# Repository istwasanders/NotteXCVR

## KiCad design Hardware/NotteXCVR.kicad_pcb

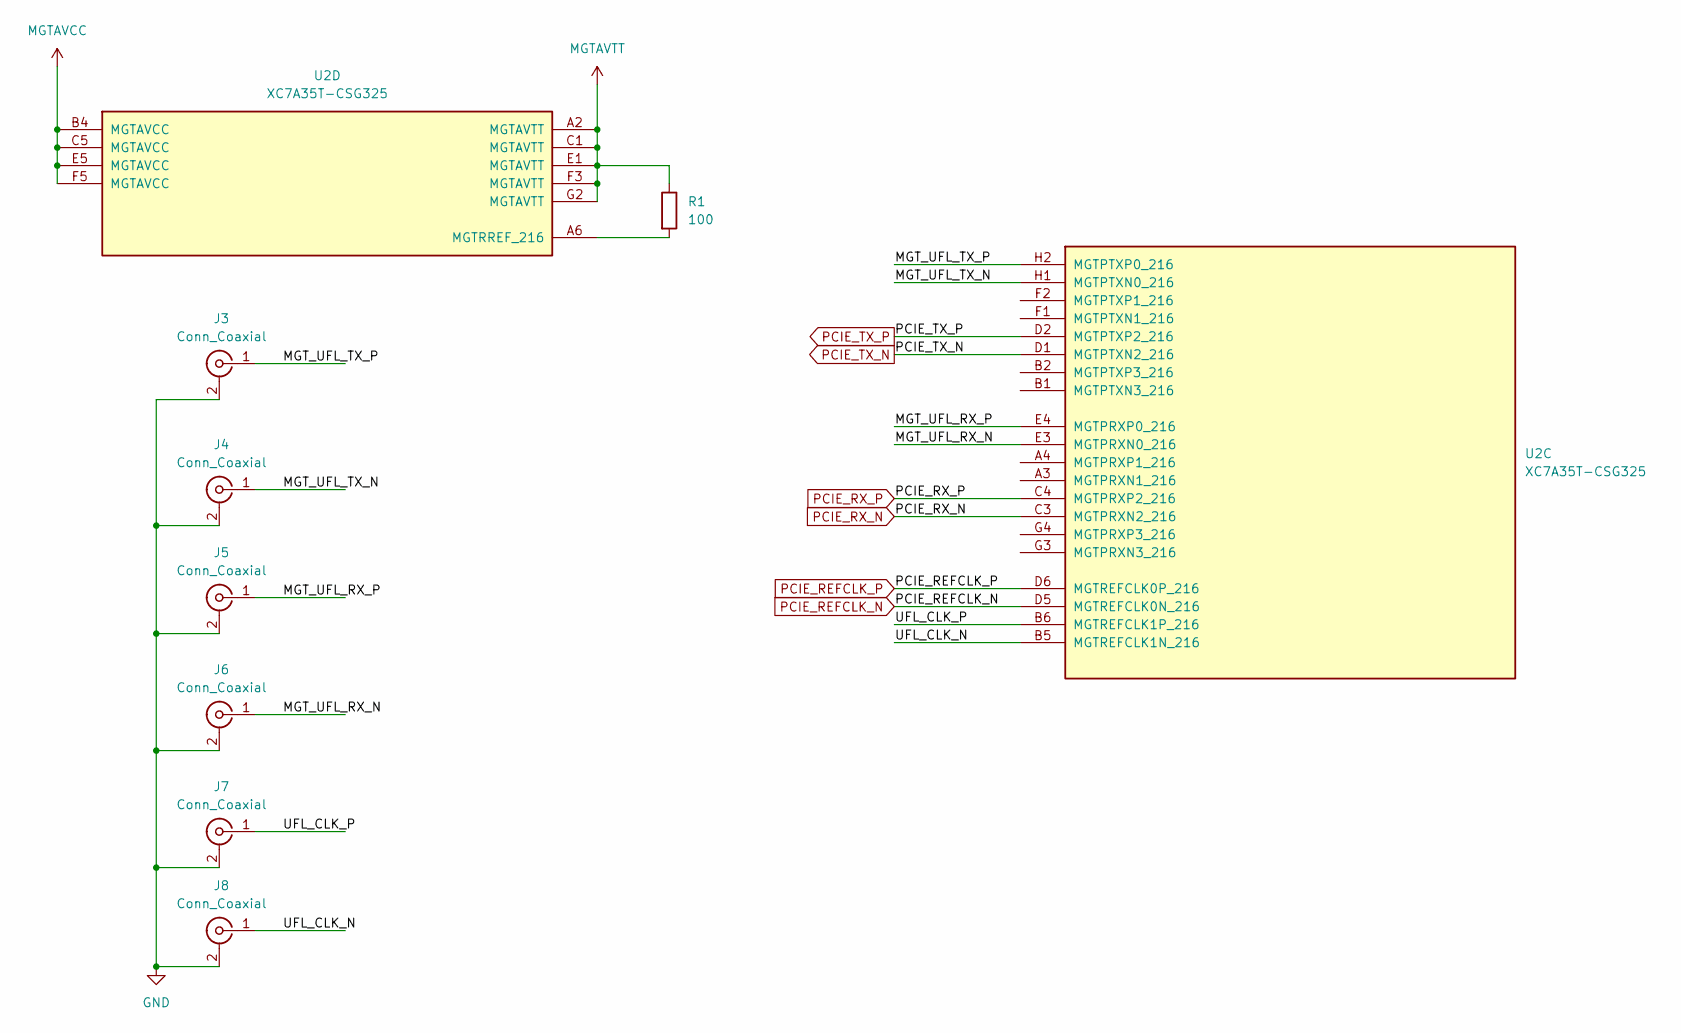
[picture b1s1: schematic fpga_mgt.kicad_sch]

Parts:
J3, J4, J5, J6, J7, J8: Conn_Coaxial; U.FL_Hirose_U.FL-R-SMT-1_Vertical
R1: 100; R_0402_1005Metric
U2: XC7A35T-CSG325; Xilinx_CSG325

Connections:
/FPGA_MGT/MGT_UFL_RX_N: J6.1 (In), U2.E3 (MGTPRXN0_216)
/FPGA_MGT/MGT_UFL_RX_P: J5.1 (In), U2.E4 (MGTPRXP0_216)
/FPGA_MGT/MGT_UFL_TX_N: J4.1 (In), U2.H1 (MGTPTXN0_216)
/FPGA_MGT/MGT_UFL_TX_P: J3.1 (In), U2.H2 (MGTPTXP0_216)
/FPGA_MGT/UFL_CLK_N: J8.1 (In), U2.B5 (MGTREFCLK1N_216)
/FPGA_MGT/UFL_CLK_P: J7.1 (In), U2.B6 (MGTREFCLK1P_216)
GND: J3.2 (Ext), J4.2 (Ext), J5.2 (Ext), J6.2 (Ext), J7.2 (Ext), J8.2 (Ext); also elsewhere on the board
MGTAVCC: U2.B4 (MGTAVCC), U2.C5 (MGTAVCC), U2.E5 (MGTAVCC), U2.F5 (MGTAVCC)
MGTAVTT: R1.1, U2.A2 (MGTAVTT), U2.C1 (MGTAVTT), U2.E1 (MGTAVTT), U2.F3 (MGTAVTT), U2.G2 (MGTAVTT)
unnamed: R1.2, U2.A6 (MGTRREF_216)
PCIE_REFCLK_N: U2.D5 (MGTREFCLK0N_216); also elsewhere on the board
PCIE_REFCLK_P: U2.D6 (MGTREFCLK0P_216); also elsewhere on the board
PCIE_RX_N: U2.C3 (MGTPRXN2_216); also elsewhere on the board
PCIE_RX_P: U2.C4 (MGTPRXP2_216); also elsewhere on the board
PCIE_TX_N: U2.D1 (MGTPTXN2_216); also elsewhere on the board
PCIE_TX_P: U2.D2 (MGTPTXP2_216); also elsewhere on the board

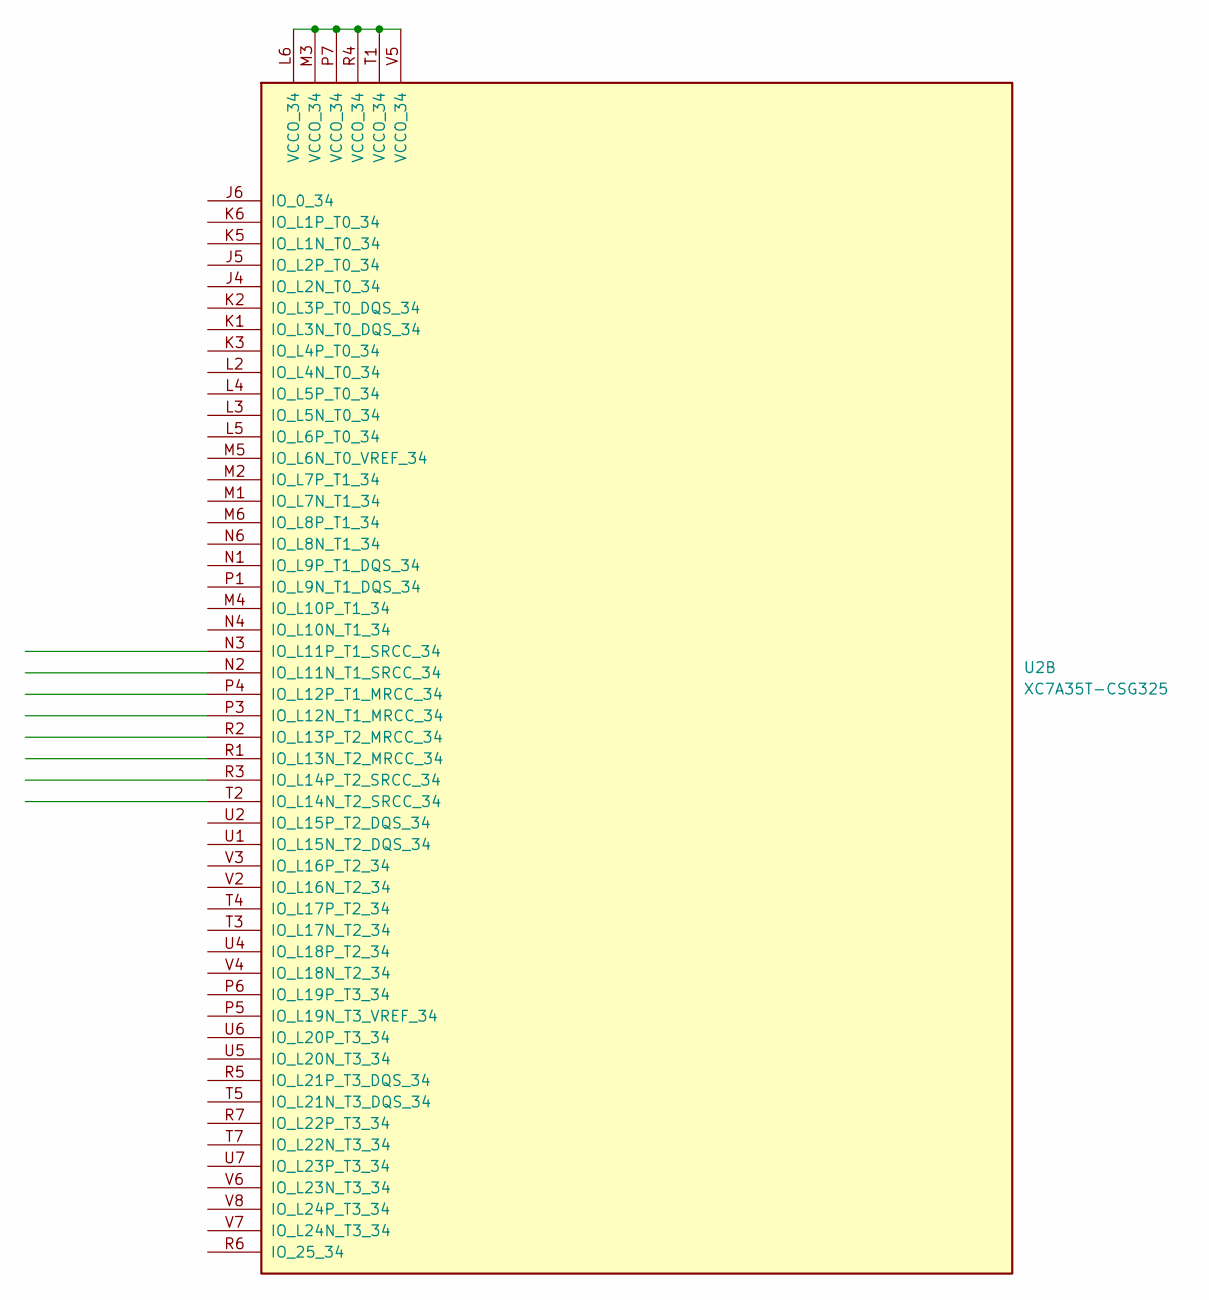
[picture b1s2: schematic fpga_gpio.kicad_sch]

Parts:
U2: XC7A35T-CSG325; Xilinx_CSG325

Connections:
unnamed: U2.L6 (VCCO_34), U2.M3 (VCCO_34), U2.P7 (VCCO_34), U2.R4 (VCCO_34), U2.T1 (VCCO_34), U2.V5 (VCCO_34)

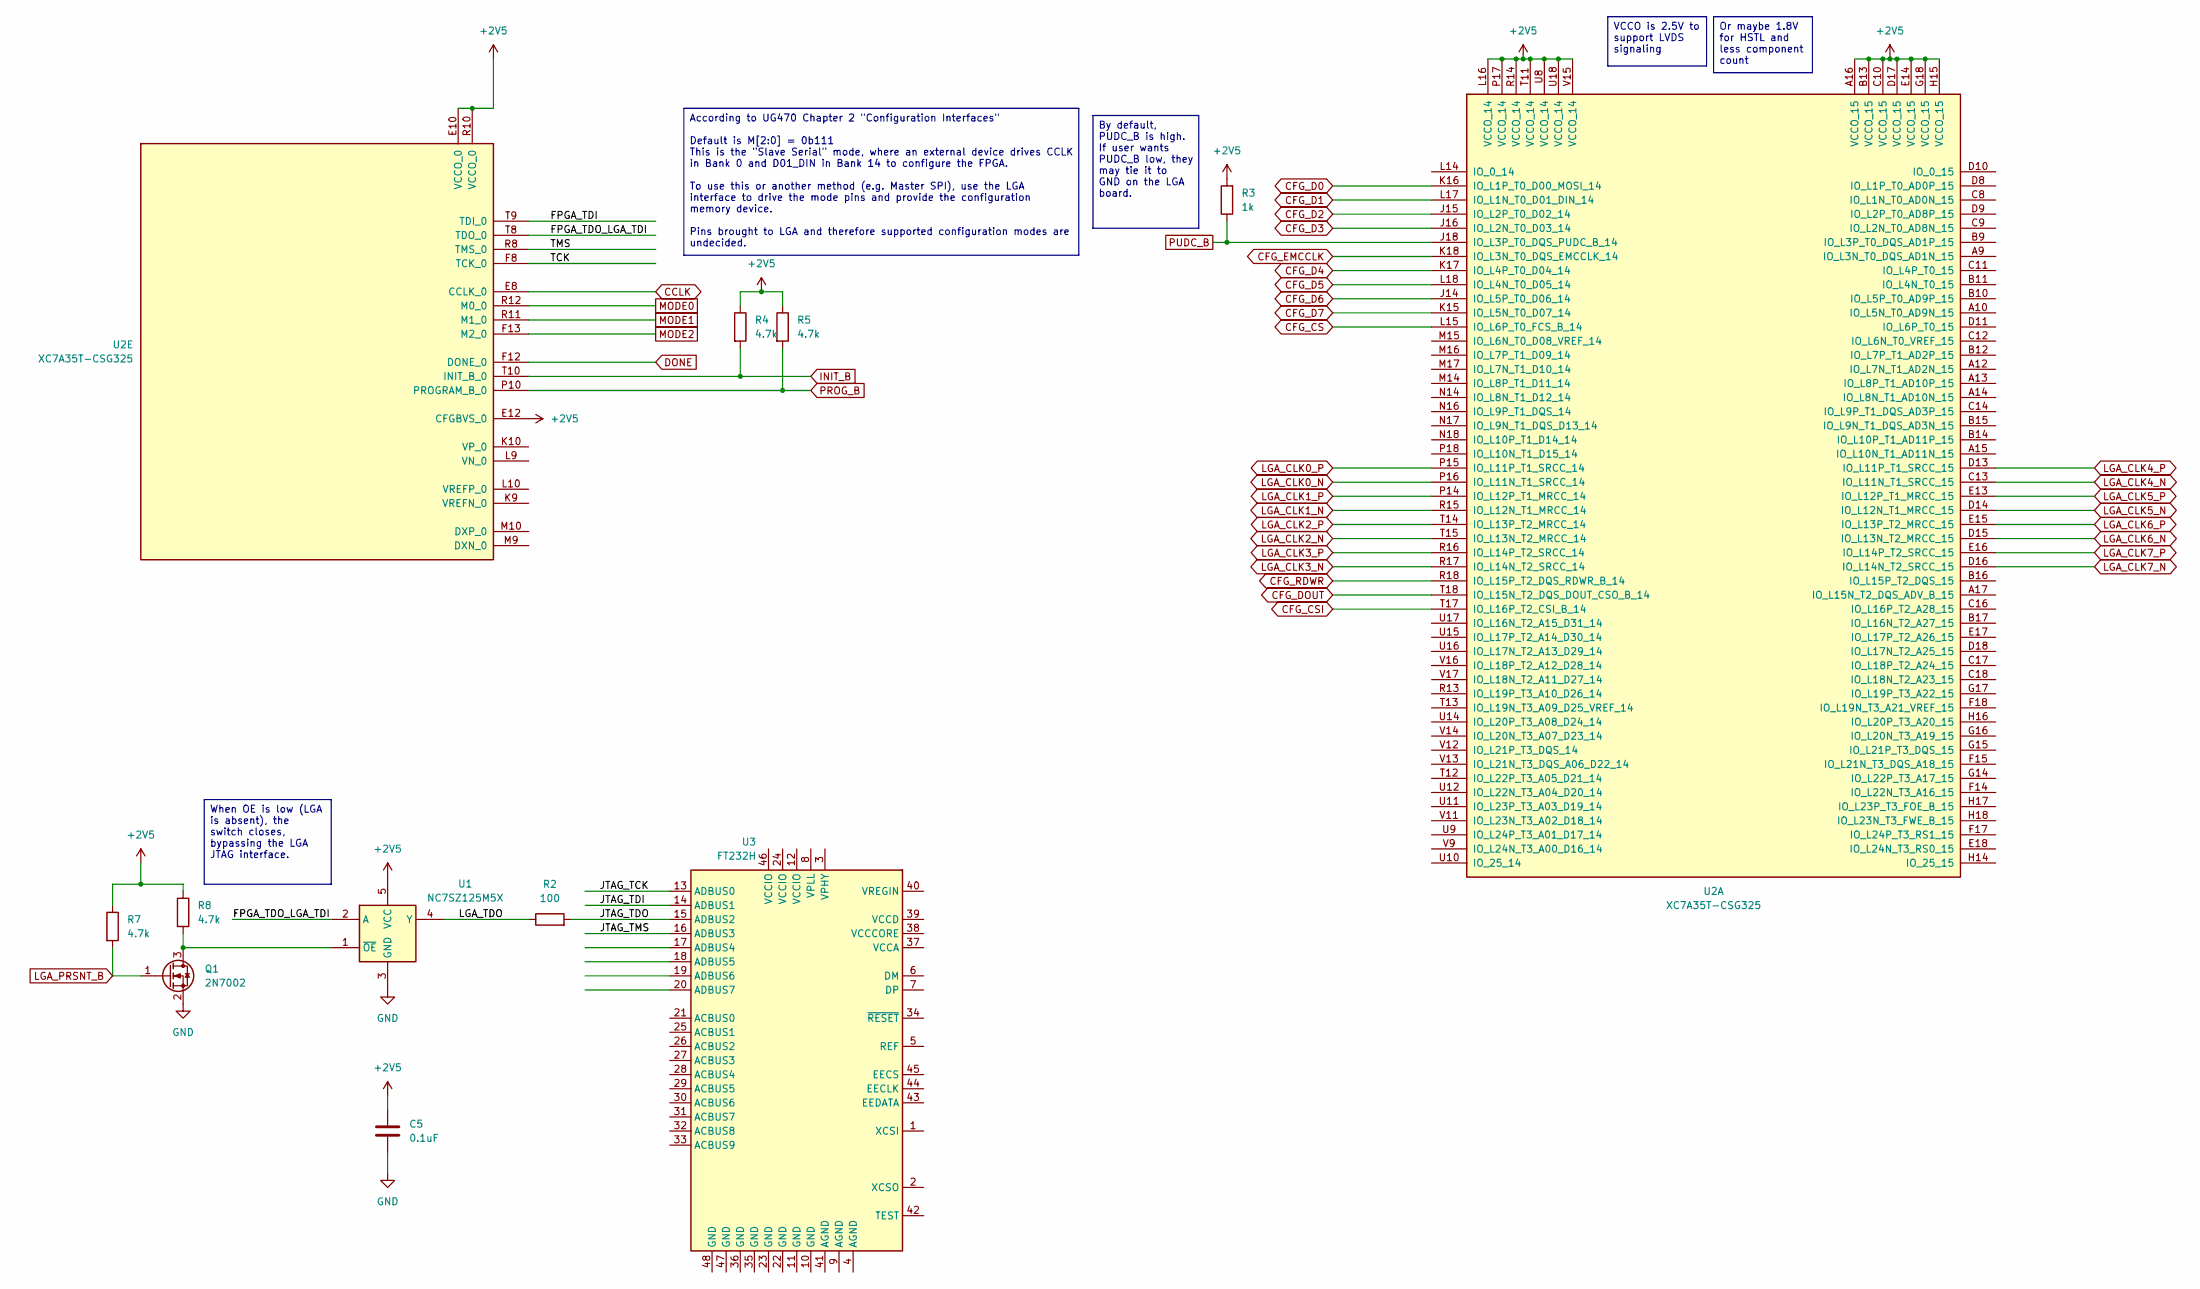
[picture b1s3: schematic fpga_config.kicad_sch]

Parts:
C5: 0.1uF; C_01005_0402Metric
Q1: 2N7002; SOT-23
R2: 100; R_0402_1005Metric
R3: 1k; R_0402_1005Metric
R4, R5, R7, R8: 4.7k; R_0402_1005Metric
U1: NC7SZ125M5X; SOT-23-5
U2: XC7A35T-CSG325; Xilinx_CSG325
U3: FT232H; LQFP-48_7x7mm_P0.5mm

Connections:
+2V5: C5.1, R3.2, R4.1, R5.1, R7.1, R8.1, U1.5 (VCC), U2.A16 (VCCO_15), U2.B13 (VCCO_15), U2.C10 (VCCO_15), U2.D17 (VCCO_15), U2.E10 (VCCO_0), U2.E12 (CFGBVS_0), U2.E14 (VCCO_15), U2.G18 (VCCO_15), U2.H15 (VCCO_15), U2.L16 (VCCO_14), U2.P17 (VCCO_14), U2.R10 (VCCO_0), U2.R14 (VCCO_14), U2.T11 (VCCO_14), U2.U8 (VCCO_14), U2.U18 (VCCO_14), U2.V15 (VCCO_14)
/FPGA_Config/FPGA_TDI: U2.T9 (TDI_0)
/FPGA_Config/FPGA_TDO_LGA_TDI: U1.2 (A), U2.T8 (TDO_0)
/FPGA_Config/JTAG_TCK: U3.13 (ADBUS0)
/FPGA_Config/JTAG_TDI: U3.14 (ADBUS1)
/FPGA_Config/JTAG_TDO: R2.2, U3.15 (ADBUS2)
/FPGA_Config/JTAG_TMS: U3.16 (ADBUS3)
/FPGA_Config/LGA_TDO: R2.1, U1.4 (Y)
/FPGA_Config/TCK: U2.F8 (TCK_0)
/FPGA_Config/TMS: U2.R8 (TMS_0)
CCLK: U2.E8 (CCLK_0)
CFG_CS: U2.L15 (IO_L6P_T0_FCS_B_14)
CFG_CSI: U2.T17 (IO_L16P_T2_CSI_B_14)
CFG_D0: U2.K16 (IO_L1P_T0_D00_MOSI_14)
CFG_D1: U2.L17 (IO_L1N_T0_D01_DIN_14)
CFG_D2: U2.J15 (IO_L2P_T0_D02_14)
CFG_D3: U2.J16 (IO_L2N_T0_D03_14)
CFG_D4: U2.K17 (IO_L4P_T0_D04_14)
CFG_D5: U2.L18 (IO_L4N_T0_D05_14)
CFG_D6: U2.J14 (IO_L5P_T0_D06_14)
CFG_D7: U2.K15 (IO_L5N_T0_D07_14)
CFG_DOUT: U2.T18 (IO_L15N_T2_DQS_DOUT_CSO_B_14)
CFG_EMCCLK: U2.K18 (IO_L3N_T0_DQS_EMCCLK_14)
CFG_RDWR: U2.R18 (IO_L15P_T2_DQS_RDWR_B_14)
DONE: U2.F12 (DONE_0)
GND: C5.2, Q1.2 (S), U1.3 (GND); also elsewhere on the board
INIT_B: R4.2, U2.T10 (INIT_B_0)
LGA_CLK0_N: U2.P16 (IO_L11N_T1_SRCC_14)
LGA_CLK0_P: U2.P15 (IO_L11P_T1_SRCC_14)
LGA_CLK1_N: U2.R15 (IO_L12N_T1_MRCC_14)
LGA_CLK1_P: U2.P14 (IO_L12P_T1_MRCC_14)
LGA_CLK2_N: U2.T15 (IO_L13N_T2_MRCC_14)
LGA_CLK2_P: U2.T14 (IO_L13P_T2_MRCC_14)
LGA_CLK3_N: U2.R17 (IO_L14N_T2_SRCC_14)
LGA_CLK3_P: U2.R16 (IO_L14P_T2_SRCC_14)
LGA_CLK4_N: U2.C13 (IO_L11N_T1_SRCC_15)
LGA_CLK4_P: U2.D13 (IO_L11P_T1_SRCC_15)
LGA_CLK5_N: U2.D14 (IO_L12N_T1_MRCC_15)
LGA_CLK5_P: U2.E13 (IO_L12P_T1_MRCC_15)
LGA_CLK6_N: U2.D15 (IO_L13N_T2_MRCC_15)
LGA_CLK6_P: U2.E15 (IO_L13P_T2_MRCC_15)
LGA_CLK7_N: U2.D16 (IO_L14N_T2_SRCC_15)
LGA_CLK7_P: U2.E16 (IO_L14P_T2_SRCC_15)
LGA_PRSNT_B: Q1.1 (G), R7.2
MODE0: U2.R12 (M0_0)
MODE1: U2.R11 (M1_0)
MODE2: U2.F13 (M2_0)
unnamed: Q1.3 (D), R8.2, U1.1 (~OE)
PROG_B: R5.2, U2.P10 (PROGRAM_B_0)
PUDC_B: R3.1, U2.J18 (IO_L3P_T0_DQS_PUDC_B_14)

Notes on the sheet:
VCCO is 2.5V to support LVDS signaling
Or maybe 1.8V for HSTL and less component count
When OE is low (LGA is absent), the switch closes, bypassing the LGA JTAG interface.
According to UG470 Chapter 2 "Configuration Interfaces" Default is M[2:0] = 0b111 This is the "Slave Serial" mode, where an external device drives CCLK in Bank 0 and D01_DIN in Bank 14 to configure the FPGA. To use this or another method (e.g. Master SPI), use the LGA interface to drive the mode pi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
By default, PUDC_B is high. If user wants PUDC_B low, they may tie it to GND on the LGA board.

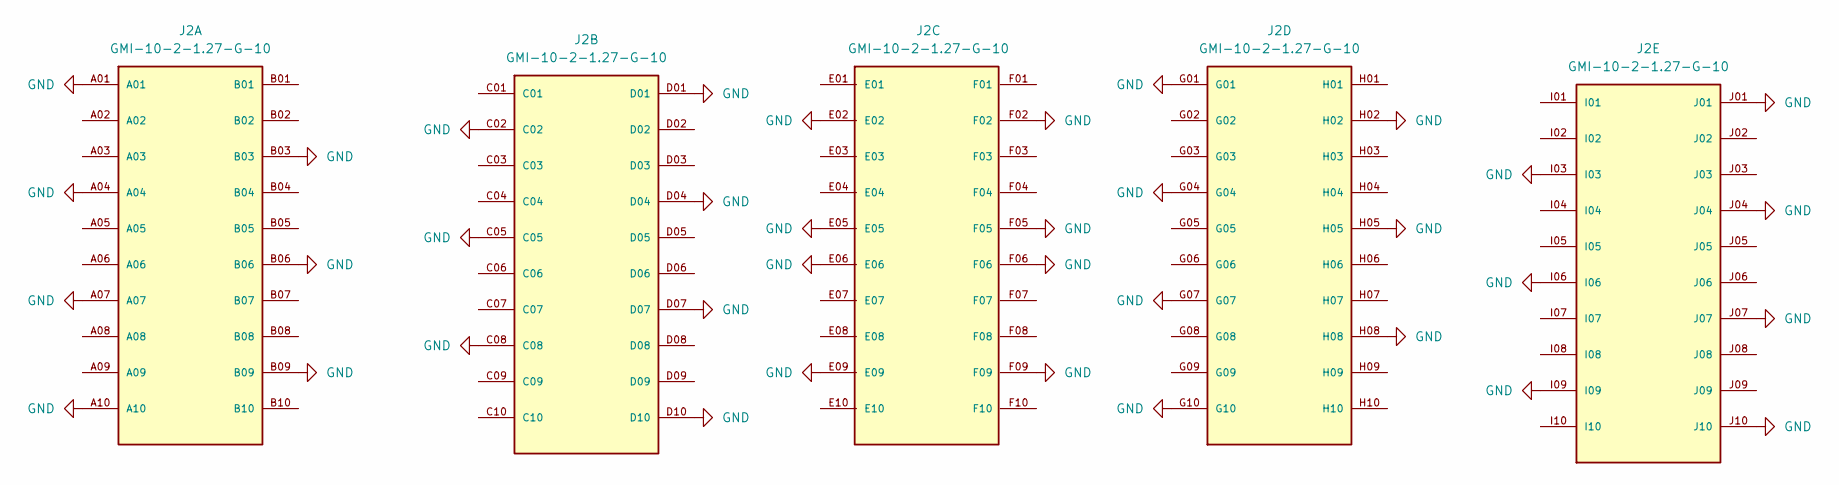
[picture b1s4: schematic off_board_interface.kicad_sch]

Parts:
J2: GMI-10-2-1.27-G-10; SAMTEC_GMI-10-2-1.27-G-10; PARTREV B

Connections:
GND: J2.A01, J2.A04, J2.A07, J2.A10, J2.B03, J2.B06, J2.B09, J2.C02, J2.C05, J2.C08, J2.D01, J2.D04, J2.D07, J2.D10, J2.E02, J2.E05, J2.E06, J2.E09, J2.F02, J2.F05, J2.F06, J2.F09, J2.G01, J2.G04, J2.G07, J2.G10, J2.H02, J2.H05, J2.H08, J2.I03, J2.I06, J2.I09, J2.J01, J2.J04, J2.J07, J2.J10; also elsewhere on the board

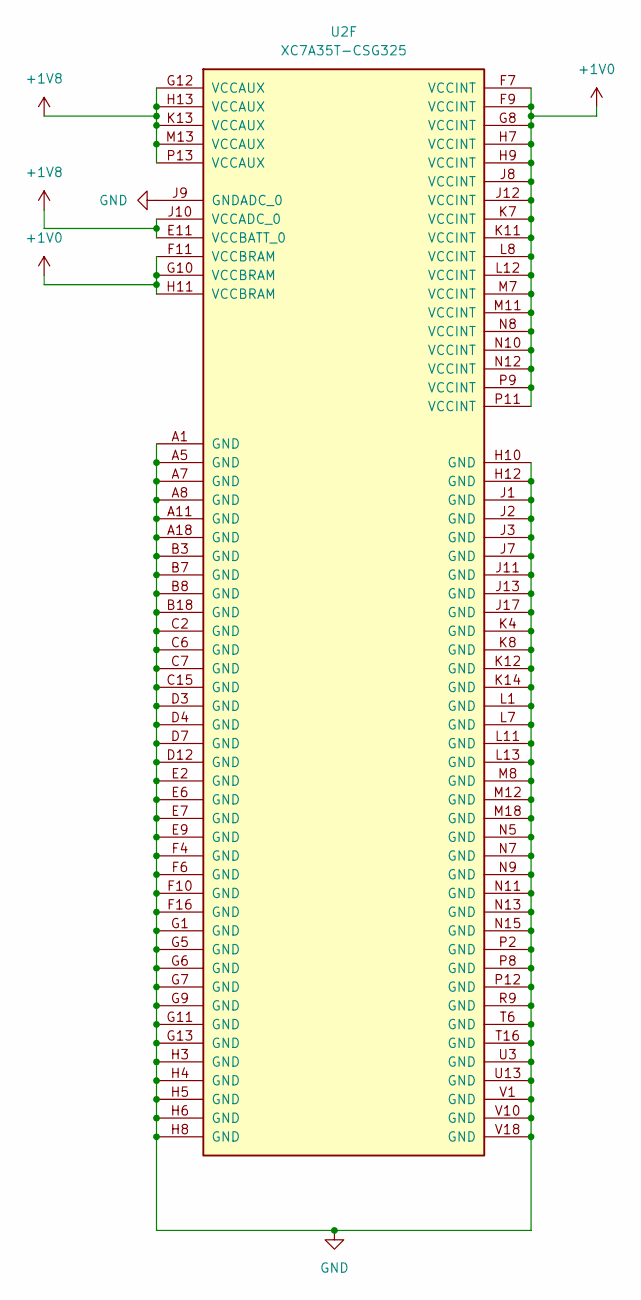
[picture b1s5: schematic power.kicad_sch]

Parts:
U2: XC7A35T-CSG325; Xilinx_CSG325

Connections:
+1V0: U2.F7 (VCCINT), U2.F9 (VCCINT), U2.F11 (VCCBRAM), U2.G8 (VCCINT), U2.G10 (VCCBRAM), U2.H7 (VCCINT), U2.H9 (VCCINT), U2.H11 (VCCBRAM), U2.J8 (VCCINT), U2.J12 (VCCINT), U2.K7 (VCCINT), U2.K11 (VCCINT), U2.L8 (VCCINT), U2.L12 (VCCINT), U2.M7 (VCCINT), U2.M11 (VCCINT), U2.N8 (VCCINT), U2.N10 (VCCINT), U2.N12 (VCCINT), U2.P9 (VCCINT), U2.P11 (VCCINT)
+1V8: U2.E11 (VCCBATT_0), U2.G12 (VCCAUX), U2.H13 (VCCAUX), U2.J10 (VCCADC_0), U2.K13 (VCCAUX), U2.M13 (VCCAUX), U2.P13 (VCCAUX)
GND: U2.A1 (GND), U2.A5 (GND), U2.A7 (GND), U2.A8 (GND), U2.A11 (GND), U2.A18 (GND), U2.B3 (GND), U2.B7 (GND), U2.B8 (GND), U2.B18 (GND), U2.C2 (GND), U2.C6 (GND), U2.C7 (GND), U2.C15 (GND), U2.D3 (GND), U2.D4 (GND), U2.D7 (GND), U2.D12 (GND), U2.E2 (GND), U2.E6 (GND), U2.E7 (GND), U2.E9 (GND), U2.F4 (GND), U2.F6 (GND), U2.F10 (GND), U2.F16 (GND), U2.G1 (GND), U2.G5 (GND), U2.G6 (GND), U2.G7 (GND), U2.G9 (GND), U2.G11 (GND), U2.G13 (GND), U2.H3 (GND), U2.H4 (GND), U2.H5 (GND), U2.H6 (GND), U2.H8 (GND), U2.H10 (GND), U2.H12 (GND), U2.J1 (GND), U2.J2 (GND), U2.J3 (GND), U2.J7 (GND), U2.J9 (GNDADC_0), U2.J11 (GND), U2.J13 (GND), U2.J17 (GND), U2.K4 (GND), U2.K8 (GND), U2.K12 (GND), U2.K14 (GND), U2.L1 (GND), U2.L7 (GND), U2.L11 (GND), U2.L13 (GND), U2.M8 (GND), U2.M12 (GND), U2.M18 (GND), U2.N5 (GND), U2.N7 (GND), U2.N9 (GND), U2.N11 (GND), U2.N13 (GND), U2.N15 (GND), U2.P2 (GND), U2.P8 (GND), U2.P12 (GND), U2.R9 (GND), U2.T6 (GND), U2.T16 (GND), U2.U3 (GND), U2.U13 (GND), U2.V1 (GND), U2.V10 (GND), U2.V18 (GND); also elsewhere on the board

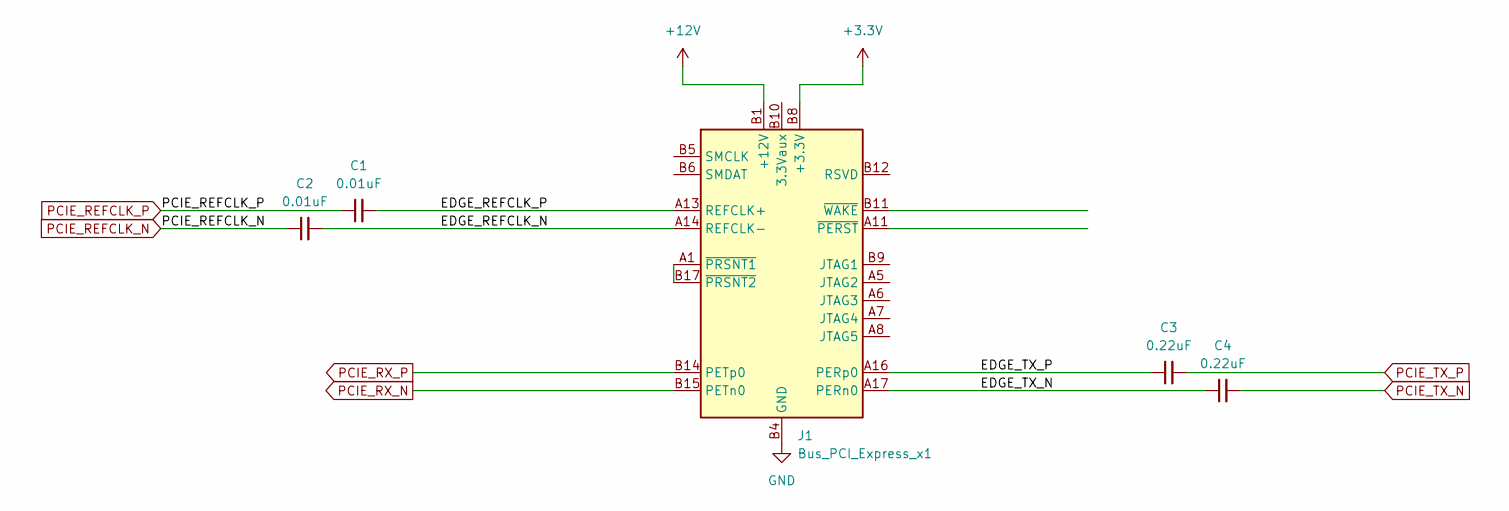
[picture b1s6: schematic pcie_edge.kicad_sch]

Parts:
C1, C2: 0.01uF; C_0402_1005Metric
C3, C4: 0.22uF; C_0402_1005Metric
J1: Bus_PCI_Express_x1; BUS_PCIexpress_x1

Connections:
+3.3V: J1.A9 (+3.3V), J1.A10 (+3.3V), J1.B8 (+3.3V)
+12V: J1.A2 (+12V), J1.A3 (+12V), J1.B1 (+12V), J1.B2 (+12V), J1.B3 (+12V)
/PCIE_Edge/EDGE_REFCLK_N: C2.2, J1.A14 (REFCLK-)
/PCIE_Edge/EDGE_REFCLK_P: C1.2, J1.A13 (REFCLK+)
/PCIE_Edge/EDGE_TX_N: C4.1, J1.A17 (PERn0)
/PCIE_Edge/EDGE_TX_P: C3.1, J1.A16 (PERp0)
GND: J1.A4 (GND), J1.A12 (GND), J1.A15 (GND), J1.A18 (GND), J1.B4 (GND), J1.B7 (GND), J1.B13 (GND), J1.B16 (GND), J1.B18 (GND); also elsewhere on the board
unnamed: J1.A1 (~PRSNT1), J1.B17 (~PRSNT2)
PCIE_REFCLK_N: C2.1; also elsewhere on the board
PCIE_REFCLK_P: C1.1; also elsewhere on the board
PCIE_RX_N: J1.B15 (PETn0); also elsewhere on the board
PCIE_RX_P: J1.B14 (PETp0); also elsewhere on the board
PCIE_TX_N: C4.2; also elsewhere on the board
PCIE_TX_P: C3.2; also elsewhere on the board

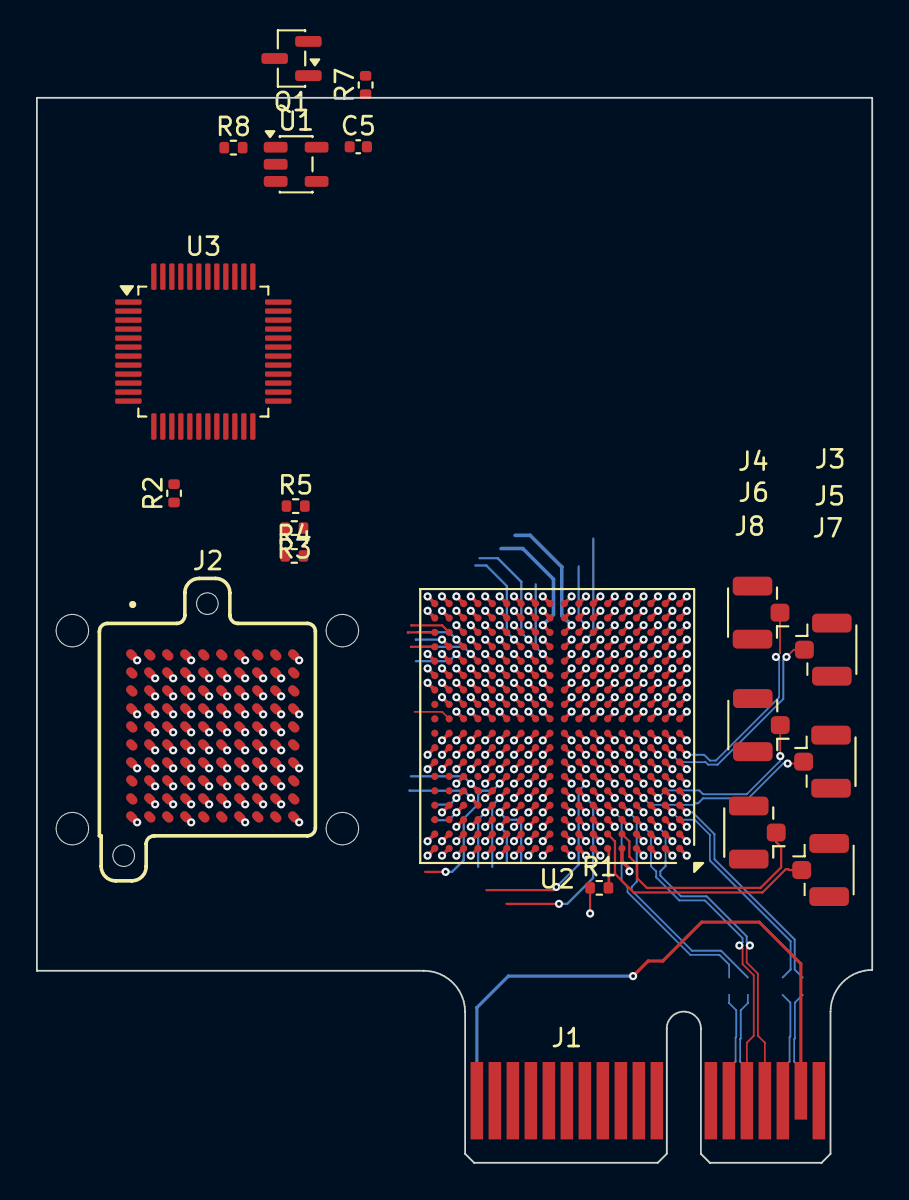
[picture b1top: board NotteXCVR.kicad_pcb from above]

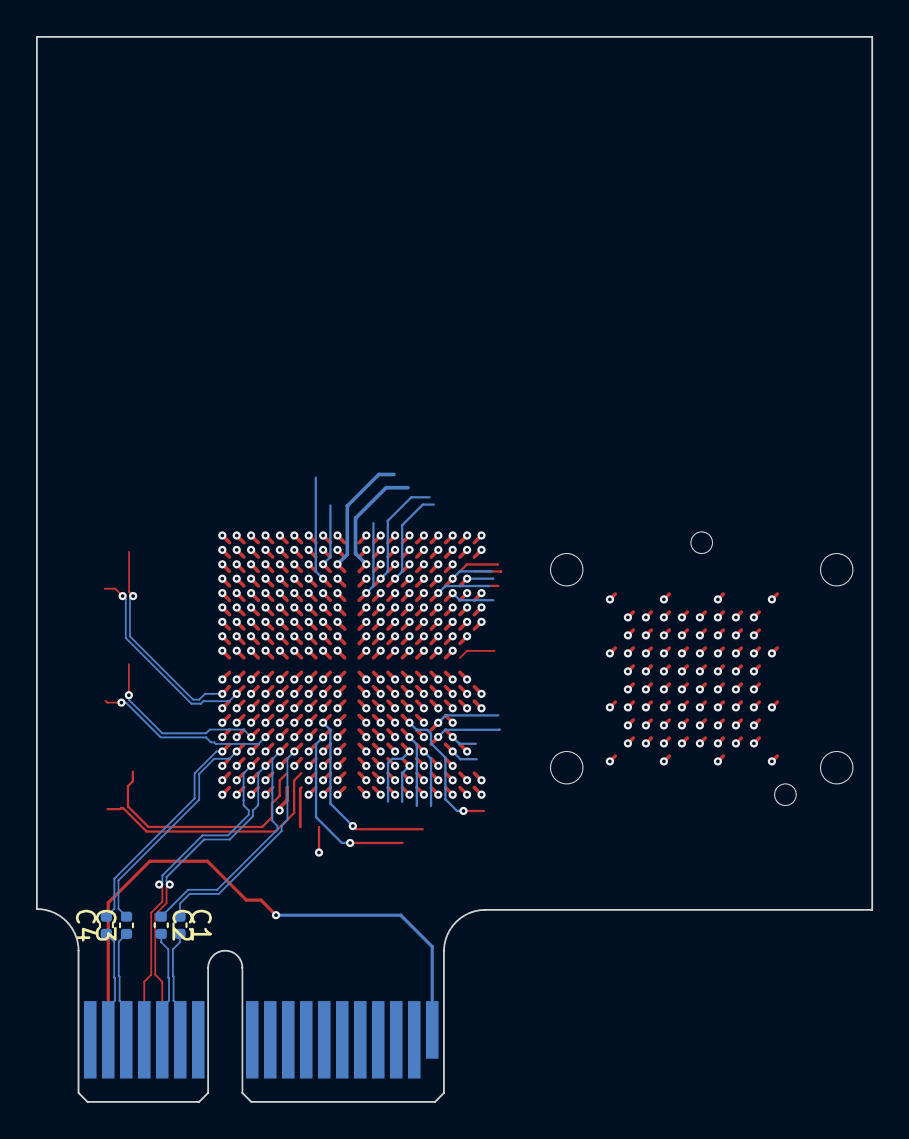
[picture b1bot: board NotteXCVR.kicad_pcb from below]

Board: 2 copper layers, 46.4 x 59.2 mm, 24 parts (4 on the bottom side), 35 nets.
